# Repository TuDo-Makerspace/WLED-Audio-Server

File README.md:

# WLED Audio Server

This compact device is designed to function as a WLED audio server. It analyzes 3.5mm audio input and synchronizes audio-reactive effects across multiple WLED devices using the "Sync" feature. I.e. this is just a "headless" WLED controller.

## Hardware

This device features two 3.5mm audio jacks: one for input and one for through-output (orientation is interchangable). This allows the server to be placed in-line between an audio source and a speaker system.

A potentiometer is used to adjust the gain of the audio input. This lets you amplify quieter signals or reduce the gain for louder ones to clipping. To help with this, a small red clipping LED is included.

Additionally, a push-button is provided, which can be assigned to a specific WLED action, such as changing the effect.

Finally, a power LED is included to indicate when the device is powered on.

The KiCAD files for the Schematic and PCB layout can be found in this repo.

## Firmware

For enhanced audio-reactive capabilities, it is highly recommended to use the **[MoonModules fork of WLED](https://mm.kno.wled.ge/)** on both the audio server and all connected WLED devices. This fork includes additional features and optimizations specifically designed for audio-reactive setups.

A [pre-configured firmware binary](WLED-MM_esp32_4MB_M_14.5.1-dev_preconfigured.bin) for the audio server is available in this repository for quick setup.

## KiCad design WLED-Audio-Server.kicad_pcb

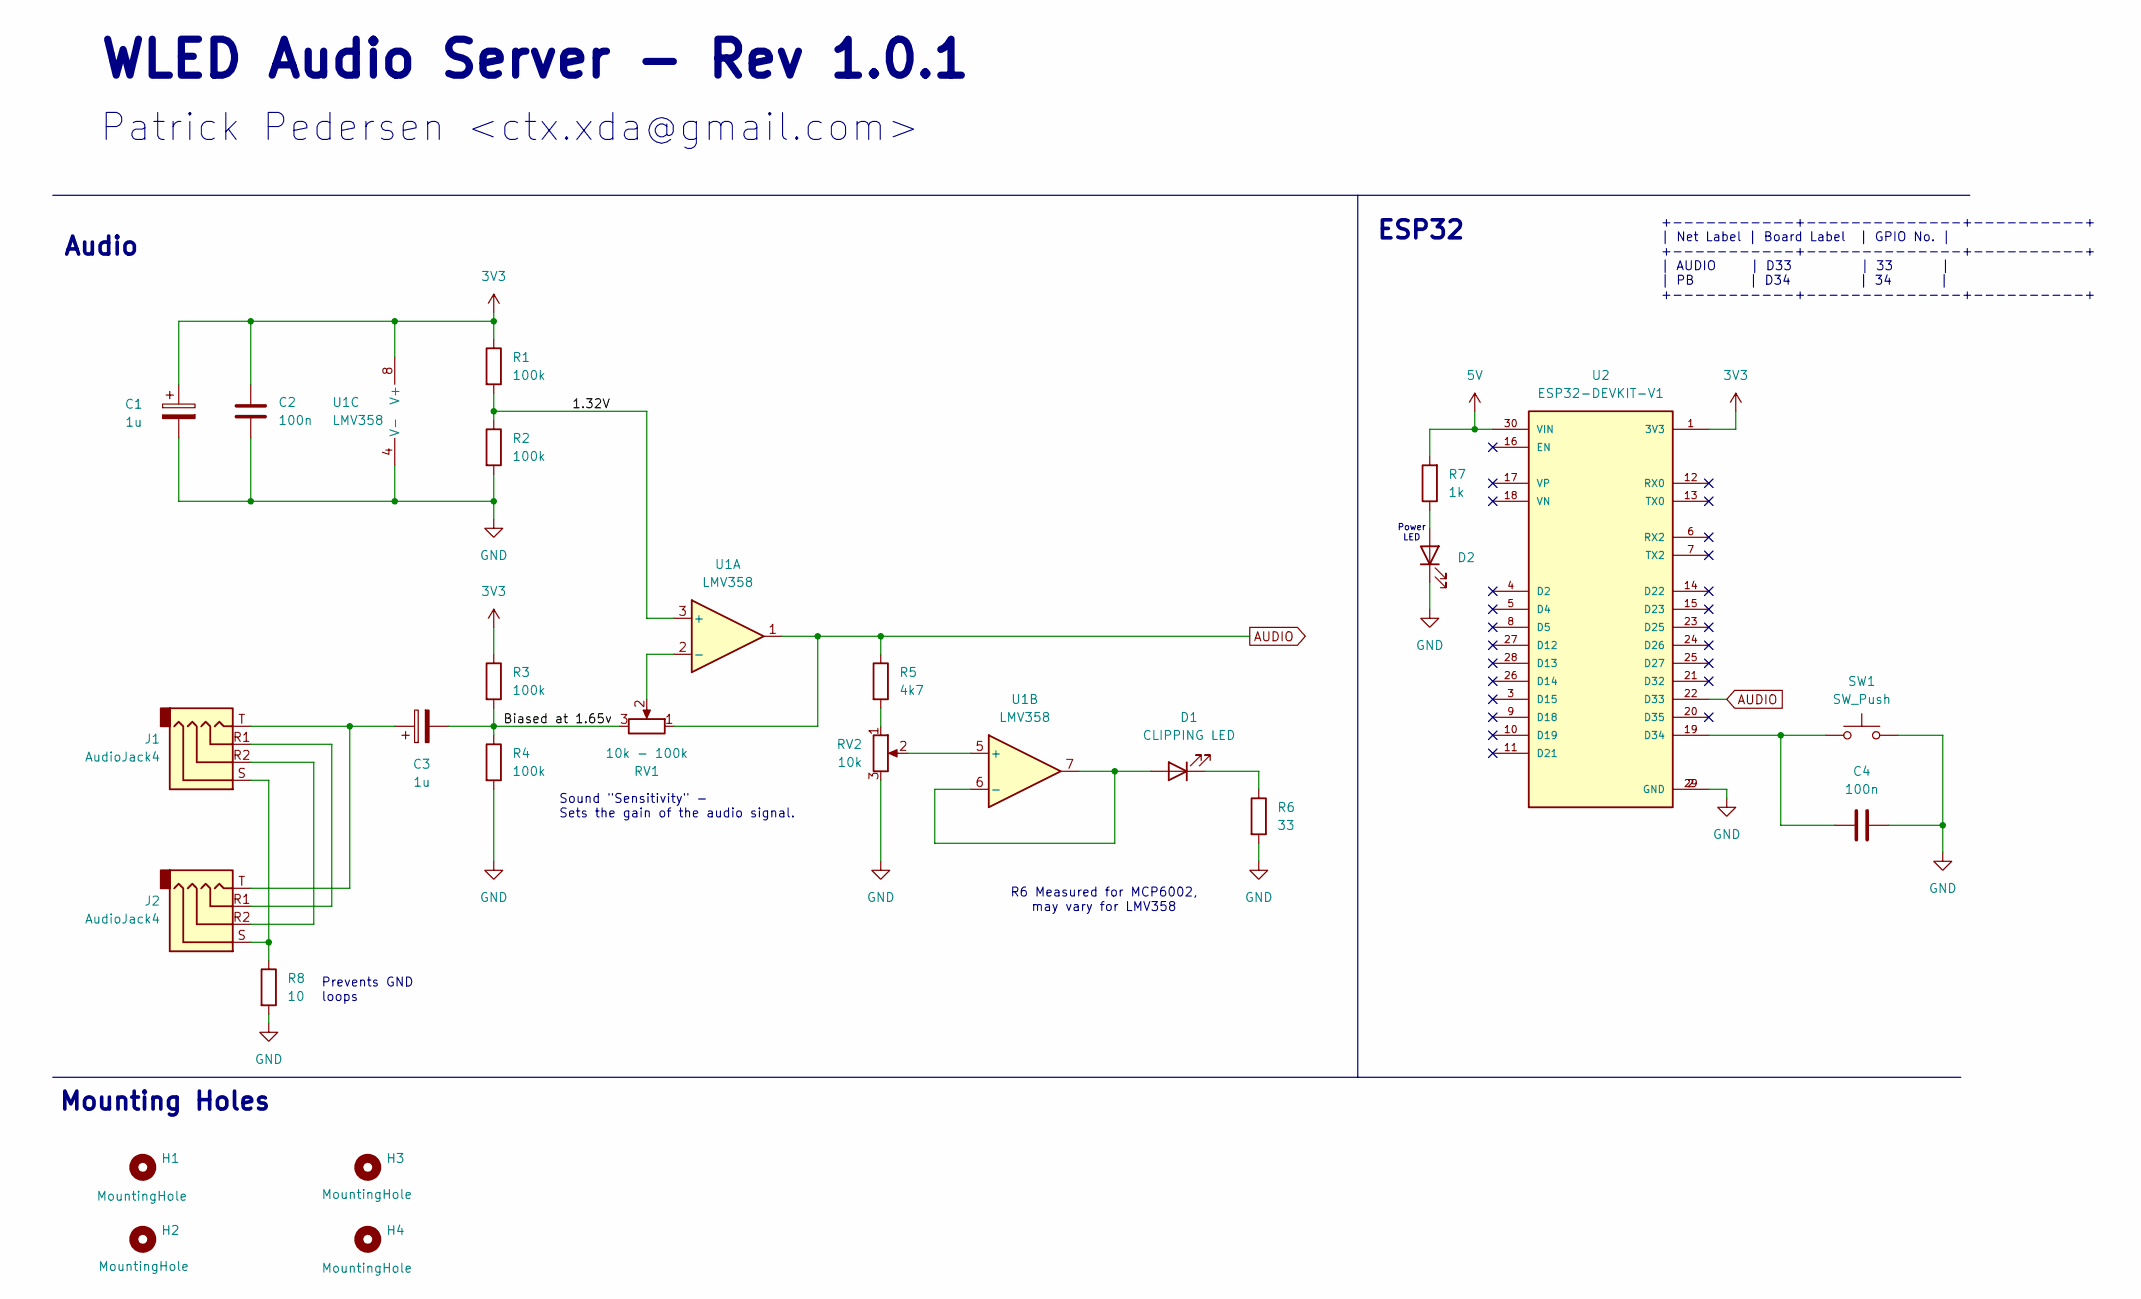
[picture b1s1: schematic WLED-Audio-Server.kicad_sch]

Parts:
C1, C3: 1u; CP_Radial_D4.0mm_P2.00mm
C2, C4: 100n; C_1206_3216Metric_Pad1.33x1.80mm_HandSolder
D1: CLIPPING LED; LED_D3.0mm
D2: LED; LED_D5.0mm
H1, H2, H3, H4: MountingHole; MountingHole_3.2mm_M3
J1, J2: AudioJack4; TRRS-PJ-320A
R1, R2, R3, R4: 100k; R_1206_3216Metric_Pad1.30x1.75mm_HandSolder
R5: 4k7; R_1206_3216Metric_Pad1.30x1.75mm_HandSolder
R6: 33; R_1206_3216Metric_Pad1.30x1.75mm_HandSolder
R7: 1k; R_1206_3216Metric_Pad1.30x1.75mm_HandSolder
R8: 10; R_1206_3216Metric_Pad1.30x1.75mm_HandSolder
RV1: 10k - 100k; Potentiometer_RV09
RV2: 10k; Potentiometer_Runtron_RM-065_Vertical
SW1: SW_Push; SW_Push_ThroughHole_2Pin_7mm
U1: LMV358; SOIC-8_3.9x4.9mm_P1.27mm
U2: ESP32-DEVKIT-V1; MODULE_ESP32_DEVKIT_V1; PARTREV N/A

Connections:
3V3: C1.1, C2.2, R1.1, R3.1, U1.8 (V+), U2.1 (3V3)
5V: R7.2, U2.30 (VIN)
/1.32V: R1.2, R2.1, U1.3 (+)
/Biased at 1.65v: C3.2, R3.2, R4.1, RV1.3
AUDIO: R5.1, RV1.1, U1.1, U2.22 (D33)
GND: C1.2, C2.1, C4.2, D2.1 (K), R2.2, R4.2, R6.2, R8.2, RV2.3, SW1.2, U1.4 (V-), U2.2 (GND), U2.29 (GND)
unnamed: C3.1, J1.T, J2.T
unnamed: D1.2 (A), U1.6 (-), U1.7
unnamed: D1.1 (K), R6.1
unnamed: D2.2 (A), R7.1
unnamed: J1.R1, J2.R1
unnamed: J1.R2, J2.R2
unnamed: J1.S, J2.S, R8.1
unnamed: R5.2, RV2.1
unnamed: RV1.2, U1.2 (-)
unnamed: RV2.2, U1.5 (+)
unnamed: C4.1, SW1.1, U2.19 (D34)

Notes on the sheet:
Patrick Pedersen <ctx.xda@gmail.com>
Audio
Mounting Holes
ESP32
Prevents GND loops
Sound "Sensitivity" - Sets the gain of the audio signal.
R6 Measured for MCP6002, may vary for LMV358
Power LED
+-----------+--------------+----------+ | Net Label | Board Label | GPIO No. | +-----------+--------------+----------+ | AUDIO | D33 | 33 | | PB | D34 | 34 | +-----------+--------------+----------+
WLED Audio Server - Rev 1.0.1

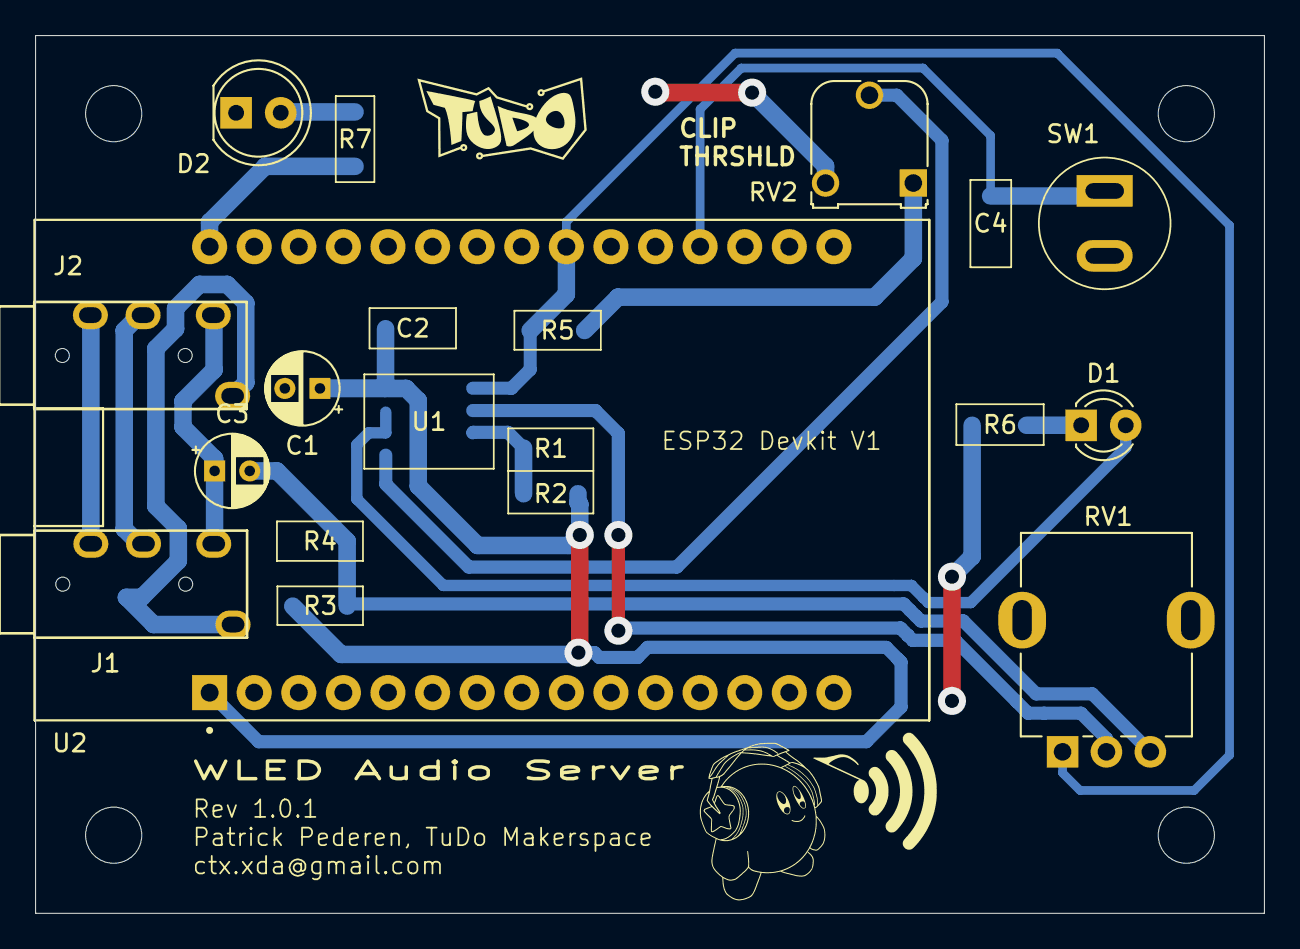
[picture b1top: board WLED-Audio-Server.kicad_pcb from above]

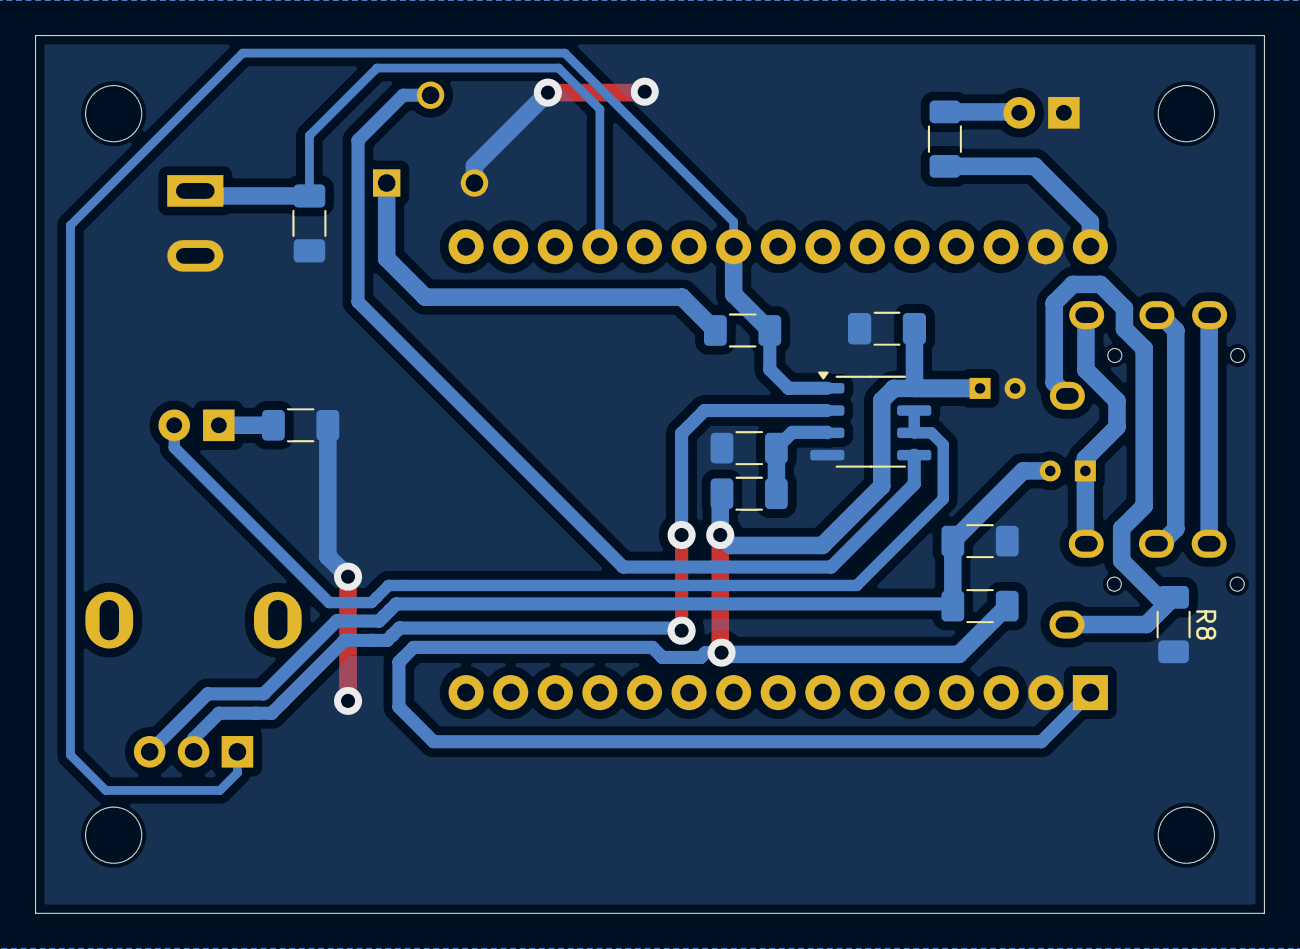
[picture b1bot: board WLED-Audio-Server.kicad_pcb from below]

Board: 2 copper layers, 70.0 x 50.0 mm, 25 parts (11 on the bottom side), 17 nets.

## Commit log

2025-03-06 Added 3d models
2025-03-06 Re-aligned mounting holes
2025-03-08 Revision 1.0.1: Fixed potentiometer orientation + PB Pitch
2025-03-15 Added pre-configured fw dump
2025-03-16 Added readme
2025-03-16 Added second showcase image
